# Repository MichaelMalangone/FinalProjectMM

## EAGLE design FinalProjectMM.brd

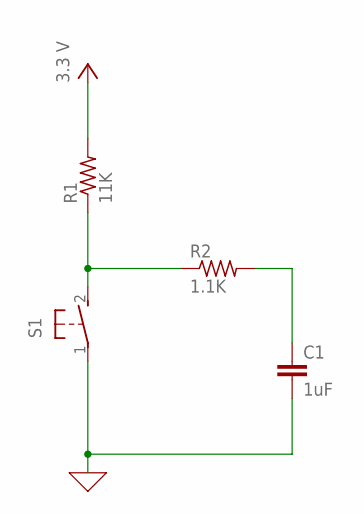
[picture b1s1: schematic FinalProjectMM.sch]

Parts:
C1: 1uF; C2.5-3
R1: 11K; 0204V
R2: 1.1K; 0204V
S1: 31-XX; B3F-31XX

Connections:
0: C1.2, S1.1
unnamed: R1.1, R2.1, S1.2 (S)
unnamed: C1.1, R2.2
VCC: R1.2

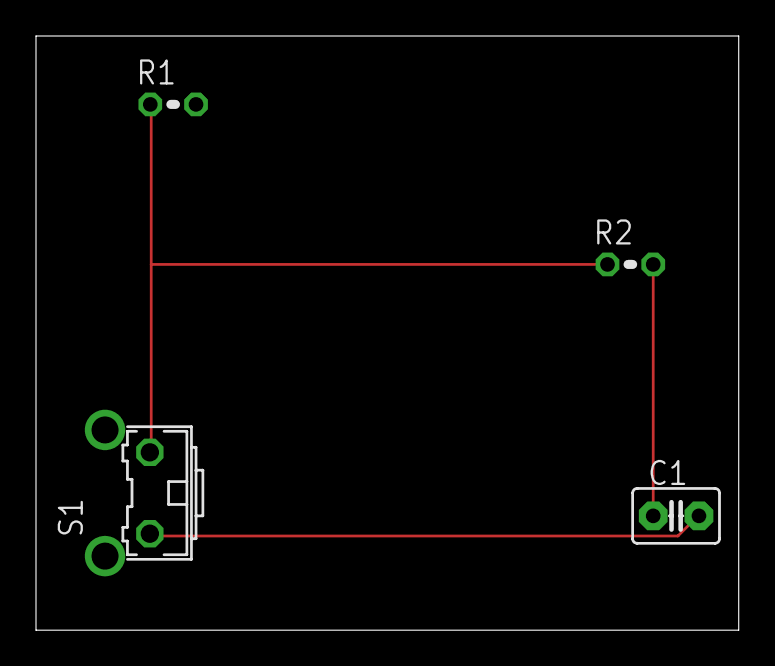
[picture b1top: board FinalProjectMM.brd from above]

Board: 2 copper layers, 39.0 x 33.0 mm, 4 parts (0 on the bottom side), 3 nets.
